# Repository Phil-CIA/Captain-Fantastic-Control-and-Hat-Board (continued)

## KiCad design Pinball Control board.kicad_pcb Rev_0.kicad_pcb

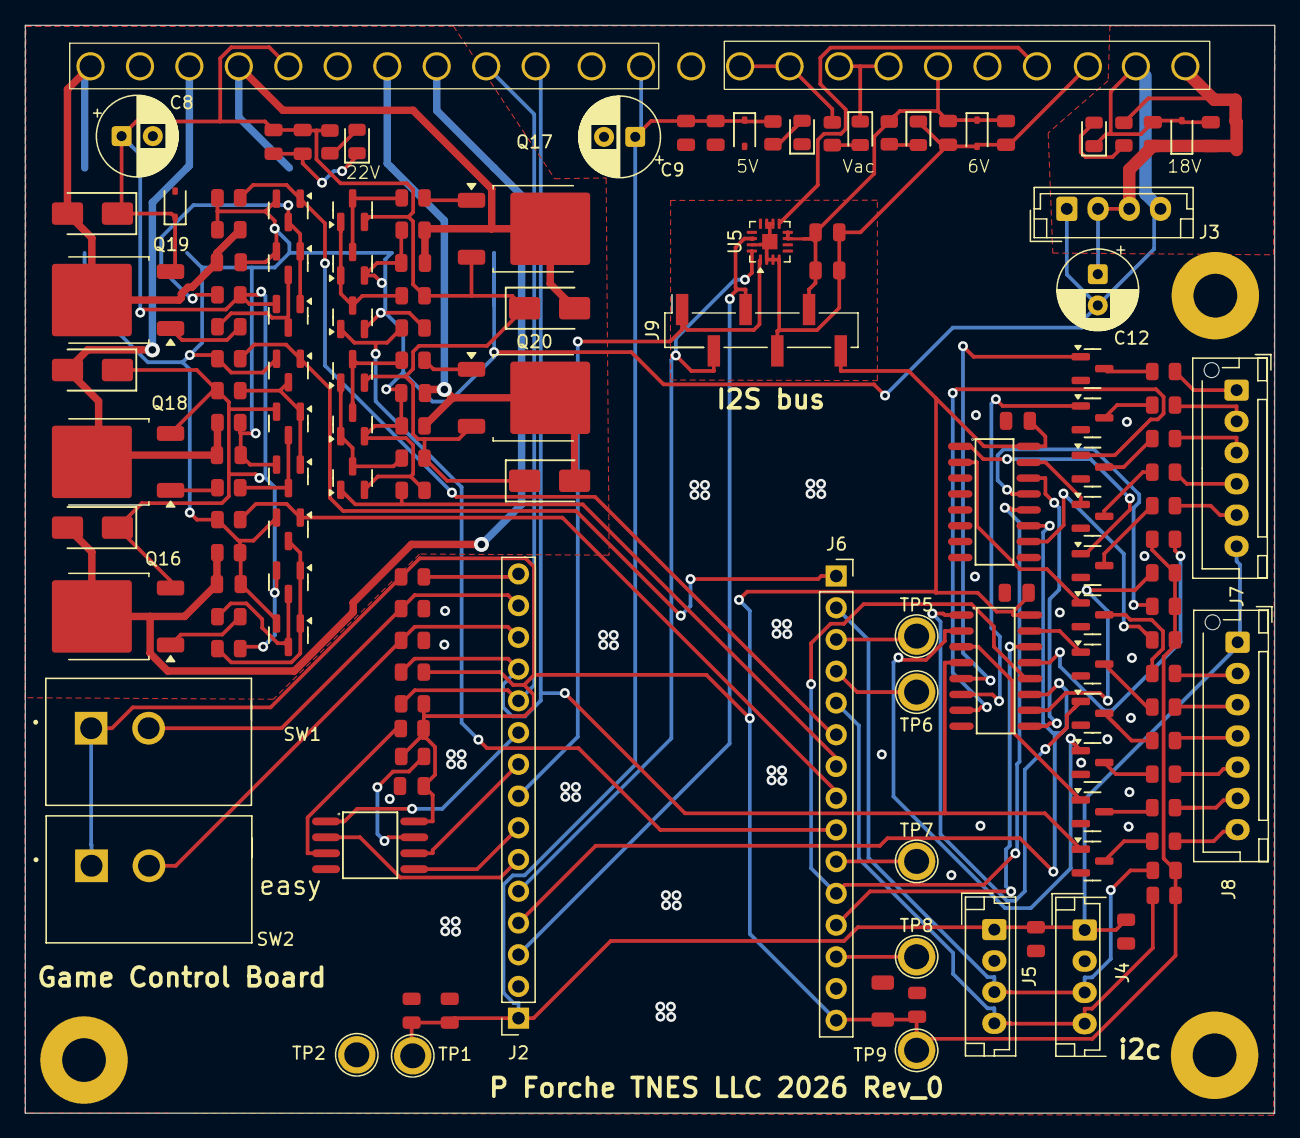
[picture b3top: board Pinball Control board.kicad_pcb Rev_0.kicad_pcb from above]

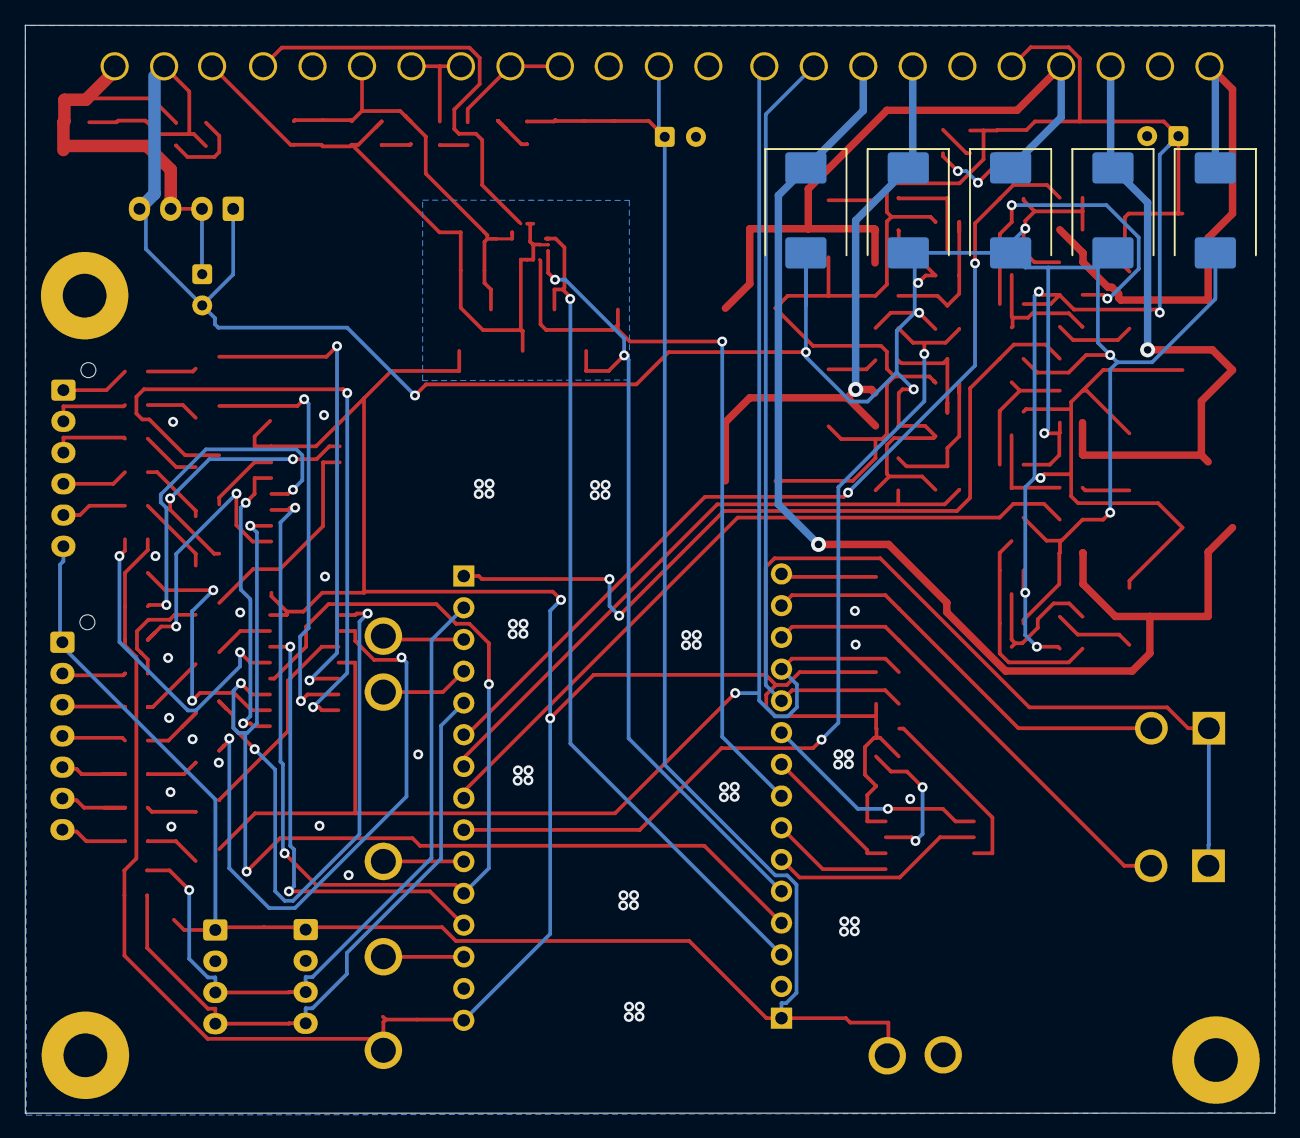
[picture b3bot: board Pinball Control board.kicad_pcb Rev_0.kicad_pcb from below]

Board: 2 copper layers, 100.0 x 87.1 mm, 151 parts (5 on the bottom side), 101 nets.

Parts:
C1, C4, C5, C10, C11, C14, C15, C16, C18, C19, C20, C21, C22, C23, C24, C25, C27: 100nF; C_0805
C2, C3, C6, C7, C13, C26: 1uF; C_0805
C8, C9, C12: 100uf, 35V; CP_Radial_D6.3mm_P2.50mm
C17: 100uF; C_1206
D1: Red; D_0805
D2: Yellow; D_0805
D3, D4, D7, D8: 1N5819WS; D_SOD-323
D5: Green; D_0805
D6, D19: White; D_0805
D9, D11, D13, D15, D17: US1M; D_SMA
D10, D12, D14, D16, D18: P6KE20A; D_SMC
H1, H2, H4: MountingHole; MountingHole_3.5mm_Pad
J1: Connector C; CONN_SDA-41792_M450_23_MOL
J2: Connector_esp32_1x15; PinSocket_1x15_P2.54mm_Vertical
J3, J4, J5: B4B-XH-A; JST_EH_B4B-EH-A_1x04_P2.50mm_Vertical
J6: PinSocket_1x15_P2.54mm_Vertical
J7: Ball In play; JST_XH_B6B-XH-AM_1x06_P2.50mm_Vertical
J8: Conn_01x07_Pin; JST_XH_B7B-XH-AM_1x07_P2.50mm_Vertical
J9: I2S HDR; PinHeader_1x06_P2.54mm_Vertical_SMD_Pin1Right
Q1, Q2, Q3, Q4, Q5, Q7, Q9, Q11, Q13, Q15, Q21, Q22, Q23, Q24, Q25, Q26, Q27, Q28, Q29, Q30, Q31: BSS138; Q_SOT-23
Q6, Q8, Q10, Q12, Q14: BSS84; Q_SOT-23
Q16, Q17, Q18, Q19, Q20: IRFR5410; TO-252-2
R1, R6, R7, R8, R9, R10, R11, R14, R15, R16, R17, R18, R19, R20, R21, R22, R23, R29, R30, R31, R32, R33, R34, R35, R36, R37: 10kΩ; R_0805
R2, R4: 680Ω; R_0805
R3, R5: 3kΩ; R_0805
R12, R13: 4.7kΩ; R_0805
R24, R25, R26, R27, R28: 56Ω; R_0805
R38, R39, R40, R41, R42, R43, R44, R45, R46, R47, R48, R49: 270Ω; R_0805
SW1, SW2: test switch; SW_GF-123-0054
TP1, TP2, TP5, TP6, TP7, TP8, TP9: TestPoint; TestPoint_Plated_Hole_D2.0mm
U1: W25Q128; SOIC-8_L5.3-W5.3-P1.27-LS8.0-BL
U3, U4: 74HC595D; SOIC-16_L9.9-W3.9-P1.27-LS6.0-BL
U5: MAX98357A; TQFN-16-1EP_3x3mm_P0.5mm_EP1.23x1.23mm

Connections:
5.6vac: D19.1, J1.7, J1.8
5.6vac com: J1.9, J1.10, R38.1
+3V3: C1.1, C17.1, C18.1, C24.2, C25.1, J6.16 (VDD_3V3), J9.6, R1.2, R8.2, R9.2, R10.2, R11.1, R12.1, R13.1, R34.1, R35.2, R36.2, R37.1, SW1.1 (A), SW2.1 (A), TP9.1, U1.8 (VCC), U3.16 (VCC), U4.16 (VCC)
+5V: C3.1, C5.1, C9.1, C13.1, C14.1, C15.1, C16.2, D4.1, J1.12, J2.1 (Vin), J4.1, J5.1, J7.6, J8.1, R2.2, TP1.1
+18vdc: C7.1, C11.1, C12.1, D7.1, J1.1, J3.2, J3.3, R5.2
+22vdc: C2.1, C4.1, C8.1, D3.1, D9.1, D11.1, D13.1, D15.1, D17.1, J1.19, Q6.2 (S), Q8.2 (S), Q10.2 (S), Q12.2 (S), Q14.2 (S), Q16.3 (S), Q17.3 (S), Q18.3 (S), Q19.3 (S), Q20.3 (S), R3.2, R19.2, R20.2, R21.2, R22.2, R23.2
BCLK: J2.5 (GPIO14), J9.2, U5.16 (BCLK)
Ball 1: Q25.1 (G), U3.5 (Q5)
Ball 2: Q24.1 (G), U3.6 (Q6)
Ball 3: Q23.1 (G), U3.7 (Q7)
Ball 4: Q22.1 (G), U4.15 (Q0)
Ball 5: Q21.1 (G), U4.1 (Q1)
DIN: J2.8 (GPIO25), J9.1, U5.1 (DIN)
GND: C1.2, C3.2, C5.2, C9.2, C13.2, C14.2, C15.2, C16.1, C17.2, C18.2, C24.1, C25.2, D1.1, D4.2, J1.5, J1.13, J2.2 (GND), J4.2, J5.2, J6.17 (GND), Q21.2 (S), Q22.2 (S), Q23.2 (S), Q24.2 (S), Q25.2 (S), Q26.2 (S), Q27.2 (S), Q28.2 (S), Q29.2 (S), Q30.2 (S), Q31.2 (S), R6.2, R7.2, TP2.1, U1.4 (GND), U3.8 (GND), U4.8 (GND)
GND (matrix GND1): C2.2, C4.2, C7.2, C8.2, C11.2, C12.2, C19.2, C20.2, C21.2, C22.2, C23.2, D2.1, D3.2, D6.1, D7.2, D10.2 (A), D12.2 (A), D14.2 (A), D16.2 (A), D18.2 (A), J1.2, J3.1, J3.4, Q1.2 (S), Q2.2 (S), Q3.2 (S), Q4.2 (S), Q5.2 (S), Q7.2 (S), Q9.2 (S), Q11.2 (S), Q13.2 (S), Q15.2 (S), R14.1, R15.1, R16.1, R17.1, R18.1, R29.1, R30.1, R31.1, R32.1, R33.1
Game Over: Q31.1 (G), U4.2 (Q2)
I2C SCL: J4.3, J5.3, J6.29 (I2C-SCL), R12.2
I2C SDA: J4.4, J5.4, J6.26 (I2C_SDA), R13.2
LRCLK: J2.3 (GPIO13), J9.3, U5.14 (LRCLK)
unnamed: D1.2, R2.1
unnamed: D2.2, R3.1
unnamed: D5.2, R4.1
unnamed: D6.2, R5.1
unnamed: D19.2, R38.2
unnamed: J2.15 (EN_/_RESET), R11.2
unnamed: J2.7 (GPIO26), U1.5 (DI)
unnamed: J2.6 (GPIO27), U1.2 (DO)
unnamed: J2.10 (GPIO32), U1.1 (CS#)
unnamed: J2.9 (GPIO33), U1.6 (CLK)
unnamed: J2.14 (GPIO36), R6.1, SW1.2 (B)
unnamed: J2.13 (GPIO39), R7.1, SW2.2 (B)
unnamed: J6.28 (GPIO1), TP5.1
unnamed: J6.27 (GPIO3), TP6.1
unnamed: J6.18 (GPIO15), TP8.1
unnamed: J6.21 (GPIO16), TP7.1
unnamed: J7.1, R43.2
unnamed: J7.2, R42.2
unnamed: J7.3, R41.2
unnamed: J7.4, R40.2
unnamed: J7.5, R39.2
unnamed: J8.2, R49.2
unnamed: J8.3, R48.2
unnamed: J8.4, R47.2
unnamed: J8.5, R46.2
unnamed: J8.6, R45.2
unnamed: J8.7, R44.2
unnamed: Q1.3 (D), Q6.1 (G), Q7.1 (G), R19.1
unnamed: Q2.3 (D), Q8.1 (G), Q9.1 (G), R20.1
unnamed: Q6.3 (D), Q7.3 (D), R24.1
unnamed: Q8.3 (D), Q9.3 (D), R25.1
unnamed: Q10.3 (D), Q11.3 (D), R26.1
unnamed: Q3.3 (D), Q10.1 (G), Q11.1 (G), R21.1
unnamed: Q12.3 (D), Q13.3 (D), R27.1
unnamed: Q4.3 (D), Q12.1 (G), Q13.1 (G), R22.1
unnamed: Q14.3 (D), Q15.3 (D), R28.1
unnamed: Q5.3 (D), Q14.1 (G), Q15.1 (G), R23.1
unnamed: Q16.1 (G), R24.2
unnamed: Q17.1 (G), R25.2
unnamed: Q18.1 (G), R26.2
unnamed: Q19.1 (G), R27.2
unnamed: Q20.1 (G), R28.2
unnamed: Q21.3 (D), R39.1
unnamed: Q22.3 (D), R40.1
unnamed: Q23.3 (D), R41.1
unnamed: Q24.3 (D), R42.1
unnamed: Q25.3 (D), R43.1
unnamed: Q26.3 (D), R44.1
unnamed: Q27.3 (D), R45.1
unnamed: Q28.3 (D), R46.1
unnamed: Q29.3 (D), R47.1
unnamed: Q30.3 (D), R48.1
unnamed: Q31.3 (D), R49.1
unnamed: R10.1, U1.3 (IO2)
unnamed: R1.1, U1.7 (IO3)
unnamed: R36.1, U3.10 (MR#)
unnamed: R34.2, U3.13 (OE#)
unnamed: U3.9 (Q7S), U4.14 (DS)
unnamed: R35.1, U4.10 (MR#)
unnamed: R37.2, U4.13 (OE#)
Player 1: Q30.1 (G), U3.15 (Q0)
Player 2: Q29.1 (G), U3.1 (Q1)
Player 3: Q28.1 (G), U3.2 (Q2)
Player 4: Q27.1 (G), U3.3 (Q3)
S2: J6.30 (GPIO23), Q3.1 (G), R16.2
S3: J6.25 (GPIO19), Q4.1 (G), R17.2
S4: J6.24 (GPIO18), Q5.1 (G), R18.2
S5: J6.23 (GPIO5), Q1.1 (G), R14.2
S6: J6.22 (GPIO17), Q2.1 (G), R15.2
SD2: C21.1, D13.2, D14.1 (K), J1.21, Q18.2 (D), R31.2
SD3: C19.1, D15.2, D16.1 (K), J1.23, Q19.2 (D), R32.2
SD4: C22.1, D17.2, D18.1 (K), J1.17, Q20.2 (D), R33.2
SD5: C20.1, D9.2, D10.1 (K), J1.16, Q16.2 (D), R29.2
SD6: C23.1, D11.2, D12.1 (K), J1.20, Q17.2 (D), R30.2
Start: J1.15, J2.11 (GPIO35), R9.1
Tilt: J1.14, J2.12 (GPIO34), Q26.1 (G), R8.1, U3.4 (Q4)
To Speaker: J1.4, U5.9 (OUTP)
Vled: C6.1, C10.1, C26.1, C27.1, D8.1, J1.6, J9.5, R4.2, U5.7 (VDD), U5.8 (VDD)
Vled Ret: C6.2, C10.2, C26.2, C27.2, D5.1, D8.2, J1.3, J9.4, U5.2 (GAIN_SLOT), U5.3 (GND), U5.4 (~SD_MODE), U5.10 (OUTN), U5.11 (GND), U5.15 (GND), U5.17 (PAD)
a0: J2.4 (GPIO12), U3.11 (SHCP), U4.11 (SHCP)
a1: J6.20 (GPIO4), U3.12 (STCP), U4.12 (STCP)
a2: J6.19 (GPIO2), U3.14 (DS)

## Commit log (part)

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2026-04-09 initial commit files as of 4/9/2026
2026-04-09 inital commit filse for the HAT board
2026-04-09 Initialize control and HAT board repo
2026-04-09 Organize uploaded KiCad baseline
2026-04-09 Clarify board history and redesign blockers
2026-04-09 Add Rev B redesign action list
2026-04-09 Update workaround strategy for development
2026-04-09 Add 5V-only firmware bring-up plan
2026-04-09 Add first 5V power-up checklist
2026-04-09 Add initial stuffing guide for bring-up
2026-04-09 Add bench stuffing checklist
2026-04-09 Start clean control-board firmware migration
2026-04-09 Add OLED debug-display bring-up support
2026-04-09 Target SSD1306 debug OLED
2026-04-10 Document smart high-side solenoid direction
2026-04-10 Lock single-channel solenoid layout direction
2026-04-10 Add KiCad note for single-channel solenoid respin
2026-04-10 Define per-channel smart-switch block
2026-04-10 Select TPS1H200A-Q1 for solenoid respin
2026-04-10 Add repo-tracked KiCad library folders and TPS1H200 planning docs
2026-04-10 Add project-local TPS1H200 SnapMagic libraries
2026-04-11 Add first TPS1H200 channel prototype to control board schematic
2026-04-11 Replicate TPS1H200 channels across solenoid outputs
2026-04-11 Ignore KiCad autosave and backup folders
2026-04-11 Add simple bench plan and update project status
2026-04-11 Align TPS1H200 footprints to project library
2026-04-11 Save routed board checkpoint and order checklist
2026-04-12 Capture Rev1 order milestone and arrival power-up plan
2026-04-12 Checkpoint KiCad schematic and PCB updates
2026-04-13 Add machine transfer handoff for firmware transition
2026-04-16 Modularize firmware: extract audio, input, ota, command, headbox runtimes from main.cpp
    - src/audio/audio_runtime.cpp: MP3 playback, I2S, SPIFFS, W25Q128
    - src/input/direct_input_runtime.cpp: pin polling, edge detection
    - src/input/input_overlay_runtime.cpp: OLED overlay timing/text
    - src/ota/ota_runtime.cpp: WiFi, HTTP download, staged OTA apply
    - src/command/command_runtime.cpp: serial dispatcher
    - src/command/{audio,ota,input}_commands: domain command handlers
2026-04-16 Add system behavior contract doc and README pointer
2026-04-16 Add top-level system behavior contract copy
2026-04-16 Update system behavior contract defaults and board split
2026-04-16 Add round-2 clarification questions to contract
2026-04-17 Lock contract answers for gameplay and audio MVP
2026-04-17 Add round-3 clarification questions to contract
2026-04-17 Lock round-3 system behavior contract answers
2026-04-17 Add round-4 clarification questions to contract
2026-04-17 Lock round-4 system behavior contract answers
2026-04-17 Start matrix interface runtime and add Round 5 contract lock-in
2026-04-17 Lock Round 5 contract answers (Q31-Q33)
2026-04-17 Add service menu runtime and enforce audio asset policy
2026-04-17 Add board protocol runtime and matrix lamp intent commands
2026-04-17 Add degraded-mode matrix diagnostics and system status summary
2026-04-17 Add matrix board behavior contract draft
2026-04-17 Add protocol version metadata and refresh telemetry
2026-04-17 Persist service volume in NVS and restore at boot
2026-04-17 Lock matrix board contract answers
2026-04-17 docs(matrix): add round 3 clarification questions
2026-04-17 docs(matrix): add round 4 clarification questions
2026-04-17 Lock matrix contract round-3 and round-4 answers
2026-04-18 docs: align matrix board interface contract
2026-04-18 docs: restore HT16K33-style matrix contract direction
2026-04-18 Add display bring-up and verification docs
2026-04-18 Move display docs to TTF repo
2026-04-27 docs: add 2026-04-27 matrix bring-up handoff
2026-04-28 scripts: add BOM/cross-reference tooling; gitignore build_log and pycache
2026-04-29 docs: Add firmware integration handoff document for developer transition
    - Complete project state assessment (control ~80%, matrix needs I2C slave)
    - Priority 1-4 roadmap with acceptance criteria
    - Locked technical contracts (register map, GPIO pins, I2C config)
    - Reusable code modules identified
    - Hardware configuration for both boards
    - Testing and validation checklist
2026-04-29 Daily update: firmware identity, test-output validation, and 2026-04-30 handoff
2026-04-30 control test: deterministic matrix lamp blink and row-0-inclusive lamp chase
2026-05-08 Solenoid bring-up: S2 100ms test pulse, single-channel test mode, GPIO5 init fix, relay workaround handoff
2026-05-08 docs: add morning start handoff across three repos
2026-05-11 docs: append switch recovery plan to morning handoff
2026-05-13 Add recovery-to-gameplay integration plan and S2 coil protection policy (May 12–13)
2026-05-16 docs: add daily execution plan for 2026-05-16
2026-05-16 Add Rev B handoff templates and sync docs state
2026-05-16 Revert "Add Rev B handoff templates and sync docs state"
    This reverts commit 1aebddff20c8c637a3fd9a02c00e14ff86c0e610.
